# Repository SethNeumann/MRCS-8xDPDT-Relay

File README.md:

# REPO NAME: MRCS-8xDPDT-Relay
## License: Creative Commons Attribution-NonCommercial-ShareAlike

MRCS-8xDPDT-Relay - 8 channel DPDT Relay board with Arduino Relay compatible input

8 G5/JRC-19F/DY2 style relays, canbe powered from 5V from Arduino Relay Controller or any DC voltage coil available up to 48.
Uses ULN-2803 as buffer and for snubber diodes.
One side of each relay has cuttable traces normally set to +relayV and GND

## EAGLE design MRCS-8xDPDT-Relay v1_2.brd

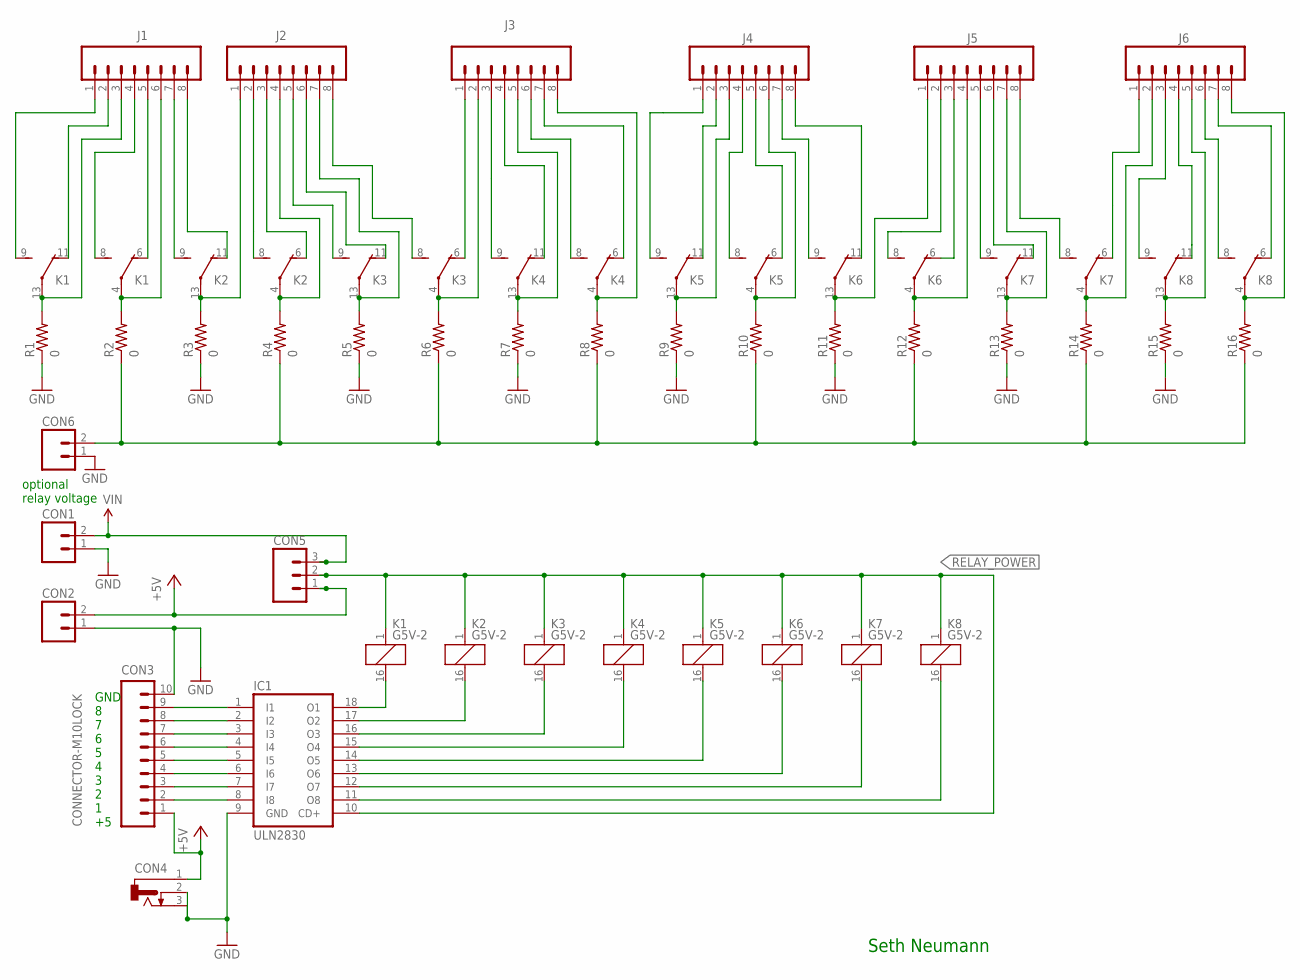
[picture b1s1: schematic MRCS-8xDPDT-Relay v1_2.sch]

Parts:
CON1, CON2, CON6: CONNECTOR-M023.5MM-LOCK; SCREWTERMINAL-3.5MM-2_LOCK
CON3: CONNECTOR-M10LOCK; 1X10_LOCK
CON4: CONNECTOR-DC-POWER-RA; DCJ0202
CON5: CONNECTOR-M03MOLEX-254-LOCK; MOLEX-1X3_LOCK
IC1: ULN2830; DIL18
J1, J2, J3, J4, J5, J6: CONNECTOR-M08LOCK; 1X08_LOCK
K1, K2, K3, K4, K5, K6, K7, K8: G5V-2
R1, R2, R3, R4, R5, R6, R7, R8, R9, R10, R11, R12, R13, R14, R15, R16: 0; CUT-R

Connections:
+5V: CON2.2 (B), CON3.1, CON4.1, CON5.1
AUX_COMMON: CON6.2 (B), R2.P2 (1), R4.P2 (1), R6.P2 (1), R8.P2 (1), R10.P2 (1), R12.P2 (1), R14.P2 (1), R16.P2 (1)
GND: CON1.1 (A), CON2.1 (A), CON3.10, CON4.2, CON4.3, CON6.1 (A), IC1.9 (GND), R1.P2 (1), R3.P2 (1), R5.P2 (1), R7.P2 (1), R9.P2 (1), R11.P2 (1), R13.P2 (1), R15.P2 (1)
unnamed: CON3.9, IC1.1 (I1)
unnamed: CON3.8, IC1.2 (I2)
unnamed: CON3.7, IC1.3 (I3)
unnamed: CON3.6, IC1.4 (I4)
unnamed: CON3.5, IC1.5 (I5)
unnamed: CON3.4, IC1.6 (I6)
unnamed: CON3.3, IC1.7 (I7)
unnamed: CON3.2, IC1.8 (I8)
unnamed: IC1.17 (O2), K2.16 (2)
unnamed: IC1.16 (O3), K3.16 (2)
unnamed: IC1.15 (O4), K4.16 (2)
unnamed: IC1.14 (O5), K5.16 (2)
unnamed: J1.7, K2.9 (S)
unnamed: IC1.13 (O6), K6.16 (2)
unnamed: IC1.12 (O7), K7.16 (2)
unnamed: IC1.11 (O8), K8.16 (2)
unnamed: J1.1, K1.9 (S)
unnamed: J1.2, K1.11 (O)
unnamed: J1.3, K1.13, R1.P1 (2)
unnamed: J1.4, K1.8 (S)
unnamed: IC1.18 (O1), K1.16 (2)
unnamed: J1.5, K1.6 (O)
unnamed: J1.6, K1.4, R2.P1 (2)
unnamed: J1.8, K2.11 (O)
unnamed: J2.1, K2.13, R3.P1 (2)
unnamed: J2.2, K2.8 (S)
unnamed: J4.3, K5.13, R9.P1 (2)
unnamed: J2.4, K2.4, R4.P1 (2)
unnamed: J2.7, K3.13, R5.P1 (2)
unnamed: J2.6, K3.11 (O)
unnamed: J2.8, K3.8 (S)
unnamed: J2.5, K3.9 (S)
unnamed: J3.1, K3.6 (O)
unnamed: J3.2, K3.4, R6.P1 (2)
unnamed: J3.3, K4.9 (S)
unnamed: J3.4, K4.11 (O)
unnamed: J3.5, K4.13, R7.P1 (2)
unnamed: J3.6, K4.8 (S)
unnamed: J3.7, K4.6 (O)
unnamed: J3.8, K4.4, R8.P1 (2)
unnamed: J5.4, K6.4, R12.P1 (2)
unnamed: J5.5, K7.9 (S)
unnamed: J5.6, K7.11 (O)
unnamed: J5.7, K7.13, R13.P1 (2)
unnamed: J5.8, K7.8 (S)
unnamed: J6.1, K7.6 (O)
unnamed: J6.2, K7.4, R14.P1 (2)
unnamed: J6.3, K8.9 (S)
unnamed: J6.4, K8.11 (O)
unnamed: J6.5, K8.13, R15.P1 (2)
unnamed: J6.6, K8.8 (S)
unnamed: J6.7, K8.6 (O)
unnamed: J6.8, K8.4, R16.P1 (2)
unnamed: J5.3, K6.6 (O)
unnamed: J5.2, K6.8 (S)
unnamed: J5.1, K6.13, R11.P1 (2)
unnamed: J4.7, K6.9 (S)
unnamed: J4.6, K5.4, R10.P1 (2)
unnamed: J4.5, K5.6 (O)
unnamed: J4.4, K5.8 (S)
unnamed: J2.3, K2.6 (O)
unnamed: J4.2, K5.11 (O)
unnamed: J4.1, K5.9 (S)
unnamed: J4.8, K6.11 (O)
RELAY_POWER: CON5.2, IC1.10 (CD+), K1.1, K2.1, K3.1, K4.1, K5.1, K6.1, K7.1, K8.1
VIN: CON1.2 (B), CON5.3

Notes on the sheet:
Seth Neumann
GND 8 7 6 5 4 3 2 1 +5
optional relay voltage

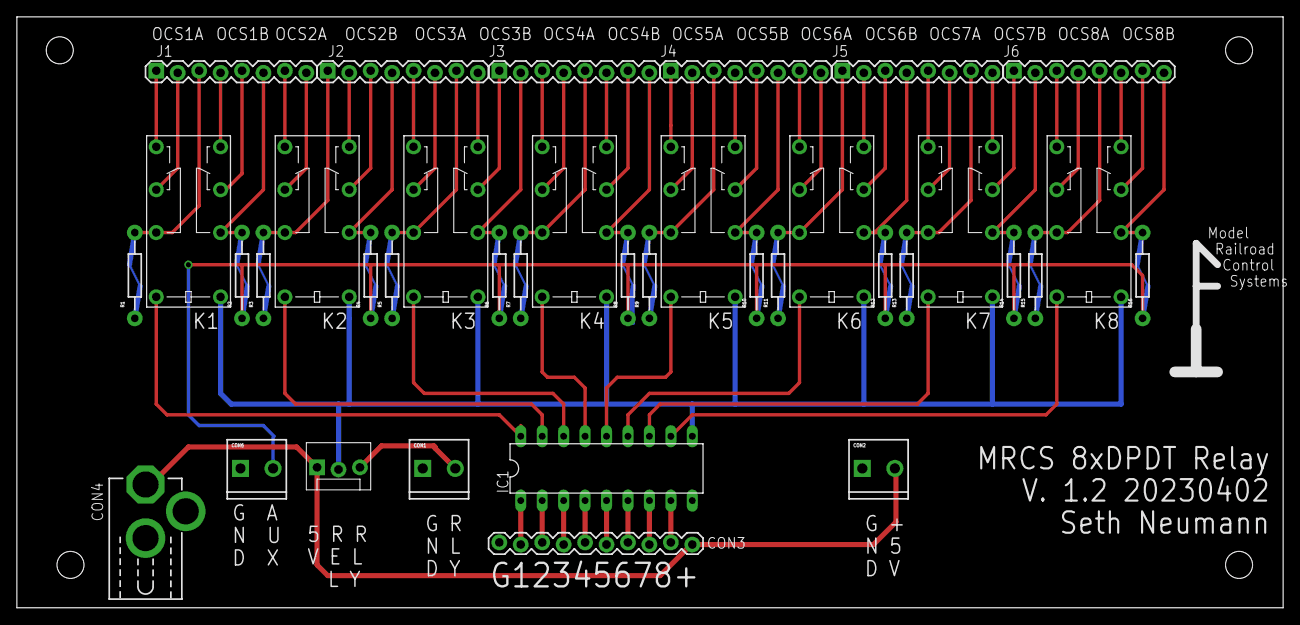
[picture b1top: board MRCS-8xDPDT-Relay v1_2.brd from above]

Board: 2 copper layers, 150.0 x 70.0 mm, 40 parts (0 on the bottom side), 69 nets.

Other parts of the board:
U$1: CA-PROP65WARNING
U$2: MRCSLOGOBTM
U$4: MRCS-LOGO-LARGE

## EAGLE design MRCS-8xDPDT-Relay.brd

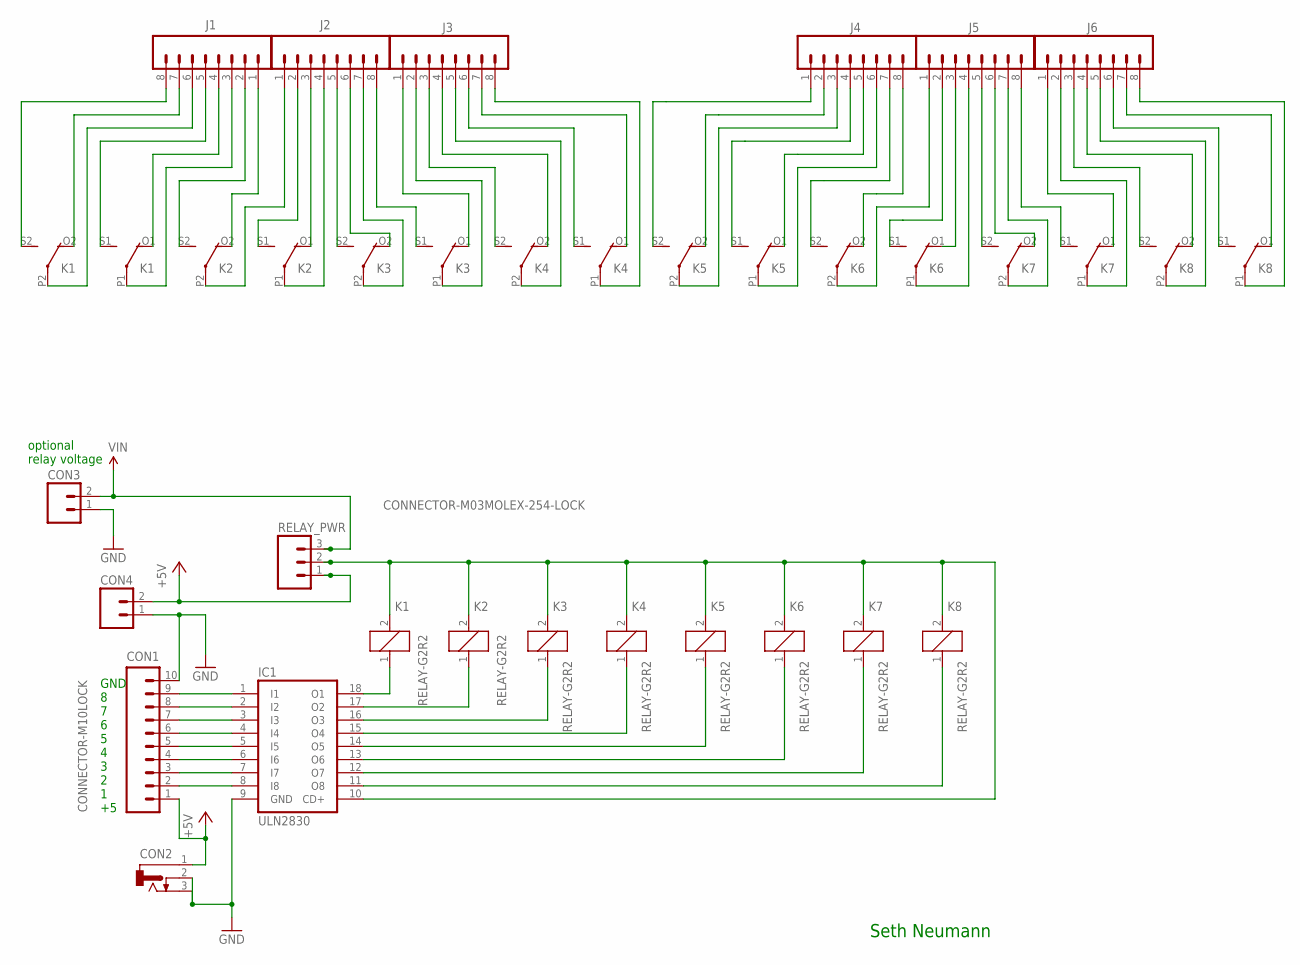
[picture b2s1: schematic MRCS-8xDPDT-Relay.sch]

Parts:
CON1: CONNECTOR-M10LOCK; 1X10_LOCK
CON2: CONNECTOR-DC-POWER-RA; DCJ0202
CON3, CON4: CONNECTOR-M023.5MM-LOCK; SCREWTERMINAL-3.5MM-2_LOCK
IC1: ULN2830; DIL18
J1, J2, J3, J4, J5, J6: CONNECTOR-M08LOCK; 1X08_LOCK
K1, K2, K3, K4, K5, K6, K7, K8: RELAY-G2R2; G2R2
RELAY_PWR: CONNECTOR-M03MOLEX-254-LOCK; MOLEX-1X3_LOCK

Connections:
+5V: CON1.1, CON2.1, CON4.2 (B), RELAY_PWR.1
GND: CON1.10, CON2.2, CON2.3, CON3.1 (A), CON4.1 (A), IC1.9 (GND)
unnamed: CON1.9, IC1.1 (I1)
unnamed: CON1.8, IC1.2 (I2)
unnamed: CON1.7, IC1.3 (I3)
unnamed: CON1.6, IC1.4 (I4)
unnamed: CON1.5, IC1.5 (I5)
unnamed: CON1.4, IC1.6 (I6)
unnamed: CON1.3, IC1.7 (I7)
unnamed: CON1.2, IC1.8 (I8)
unnamed: IC1.17 (O2), K2.1
unnamed: IC1.16 (O3), K3.1
unnamed: IC1.15 (O4), K4.1
unnamed: IC1.14 (O5), K5.1
unnamed: IC1.18 (O1), K1.1
unnamed: IC1.13 (O6), K6.1
unnamed: IC1.12 (O7), K7.1
unnamed: IC1.11 (O8), K8.1
unnamed: IC1.10 (CD+), K1.2, K2.2, K3.2, K4.2, K5.2, K6.2, K7.2, K8.2, RELAY_PWR.2
unnamed: J1.8, K1.S2 (S)
unnamed: J1.7, K1.O2 (O)
unnamed: J1.6, K1.P2
unnamed: J1.5, K1.S1 (S)
unnamed: J2.3, K2.O1 (O)
unnamed: J1.3, K1.P1
unnamed: J1.2, K2.S2 (S)
unnamed: J1.1, K2.O2 (O)
unnamed: J2.1, K2.P2
unnamed: J2.2, K2.S1 (S)
unnamed: J4.3, K5.P2
unnamed: J2.4, K2.P1
unnamed: J2.7, K3.P2
unnamed: J2.6, K3.O2 (O)
unnamed: J2.8, K3.S1 (S)
unnamed: J2.5, K3.S2 (S)
unnamed: J3.1, K3.O1 (O)
unnamed: J3.2, K3.P1
unnamed: J3.3, K4.S2 (S)
unnamed: J3.4, K4.O2 (O)
unnamed: J3.5, K4.P2
unnamed: J3.6, K4.S1 (S)
unnamed: J3.7, K4.O1 (O)
unnamed: J3.8, K4.P1
unnamed: J5.4, K6.P1
unnamed: J5.5, K7.S2 (S)
unnamed: J5.6, K7.O2 (O)
unnamed: J5.7, K7.P2
unnamed: J5.8, K7.S1 (S)
unnamed: J6.1, K7.O1 (O)
unnamed: J6.2, K7.P1
unnamed: J6.3, K8.S2 (S)
unnamed: J6.4, K8.O2 (O)
unnamed: J6.5, K8.P2
unnamed: J6.6, K8.S1 (S)
unnamed: J6.7, K8.O1 (O)
unnamed: J6.8, K8.P1
unnamed: J5.3, K6.O1 (O)
unnamed: J5.2, K6.S1 (S)
unnamed: J5.1, K6.P2
unnamed: J4.8, K6.O2 (O)
unnamed: J4.7, K6.S2 (S)
unnamed: J4.6, K5.P1
unnamed: J4.5, K5.O1 (O)
unnamed: J4.4, K5.S1 (S)
unnamed: J4.2, K5.O2 (O)
unnamed: J4.1, K5.S2 (S)
unnamed: J1.4, K1.O1 (O)
VIN: CON3.2 (B), RELAY_PWR.3

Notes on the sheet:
Seth Neumann
GND 8 7 6 5 4 3 2 1 +5
optional relay voltage

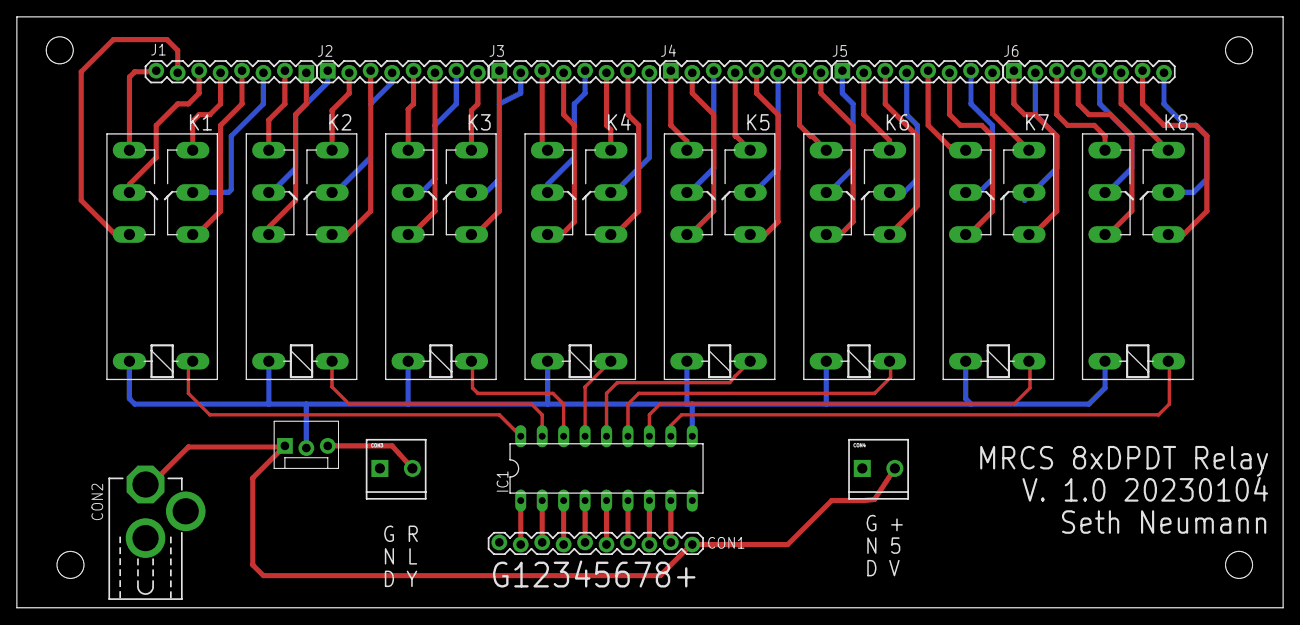
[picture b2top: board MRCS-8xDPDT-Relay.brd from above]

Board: 2 copper layers, 150.0 x 70.0 mm, 20 parts (0 on the bottom side), 68 nets.

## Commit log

2023-01-04 early draft of board for Jon
2023-01-04 early doodling
2023-01-05 keeping Jon up to date
    adding contacts
2023-01-05 1st pass complete
    first pass. no ground or power jumpers.
2023-01-05 added pdfs of schematic and top layout
    for easier review
2023-01-05 corrected relay description
2023-01-06 first release send out for fab
    this was sent out for fab. First release is for test.
2023-01-13 correct relay types, remove optional pads
2023-01-25 Version 1.1 commit
    Changed to the proper relay (G5V2 and clones). Cleaned up a lot of messy traces.
2023-01-25 Change to show V1 fabricated
    V1.1 is out for fab
2023-01-25 cleaned up description and corrected relay spec
2023-01-30 Version 1.1 submitted for fab
2023-02-10 conflict with local copy - just deleted
2023-02-10 cleaned up text
2023-02-10 Release 1.1 - updated to show resistors
    this version works with the smaller relays and has cuttable traces for ground on the COM of 1 contact Relay Power on the contact of the other
2023-04-03 changes for V1.2
    1 - changed polarity of relay so polarized relays will work
    2 - Moved the second contact to a separate bus, so you can put any signal you want in by leaving the resistor uncut or cut it and use the contact independently
    3 - added connector for bus above, cleaned up labels
2023-04-03 V1.2 updates
2023-04-03 v1.2

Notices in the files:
parts and their libraries:
SparkFun-Aesthetics: Licensing: CC v3.0 Share-Alike You are welcome to use this library for commercial purposes.
